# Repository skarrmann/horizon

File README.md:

# Horizon Keyboard

Horizon is a 52 key (4x14) ortholinear keyboard, powered by an Arduino Pro Micro.

This keyboard is a grid of 1U keys with no special features: no hotswap, no RGB, no OLED screen, no knobs.

## Project structure

* [`gerbers`](gerbers): Gerber files for PCB manufacturing
* [`graphics`](graphics): Source assets for PCB silkscreen
* [`kicad`](kicad): KiCad project files (schematics and PCB designs)
* [`kicad-libraries`](kicad-libraries): KiCad components and footprints
* [`kicad-plugins`](kicad-plugins): KiCad Pcbnew Python plugins
* [`images`](images): Images for project documentation

## PCBs

Two separate PCB designs are available for MX and Choc keyswitches, with their respective footprints and key spacing (MX: 19mm x 19mm, Choc: 18mm x 17mm).

Each design consists of a main PCB, a top plate to protect the microcontroller, and a bottom plate to protect the bottom components:

The bottom plate is a cutout of all the components exposed through the bottom of the main PCB, and screws *directly* against the main PCB. This nicely guards you and your desk surface from all the pointy through-hole bits, while retaining a low keyboard height:

## KiCad project notes

The bottom and top plates are generated via a custom KiCad 7 Python SWIG plugin [Horizon Board Producer](kicad-plugins/horizon-board-producer-plugin.py).

For the plugin to generate these plate boards, the PCB and its footprints use the following layer convention:

* `F.Adhesive` designates top plate holes and edge cuts.
* `B.Adhesive` designates bottom plate holes and edge cuts.

When the board producer runs, these layers are used as follows:

* On the board and footprints:
    * Graphics on the plate's designated layer will be moved to `Edge.Cuts` when producing that plate.
    * As with all edge cuts, please make sure your graphics are non-overlapping closed shapes.
* On footprints only:
    * Pads of type "SMD Aperture" and shape "Circular/Oval" on the plate's designated layer will be converted to proper NPTH pads.
    * Note only circular/oval shapes are supported for these pads, because they are the only available hole/drill shapes. If you need a fancy plate cutout shape on your footprint, then draw graphics lines on the designated layer.
    * **IMPORTANT**: When adding pads solely for plate cutout purposes, set the technical layer to just the designated plate cutout layers. Leave all other technical layers unchecked.

Additionally, the board producer plugin will preserve any in-bounds "H" footprint pads (mounting holes), "LOGO" footprint graphics (custom silkscreen art), and board silkscreen on the plates. Other items which are not needed for plates (e.g., copper tracks and zones) are removed from the plates.

The board producer plugin also generates all the Gerber files for production.

Please note the board producer plugin expects the following folder structure:

* The KiCad PCB file is two folders deep from the project root, e.g., `kicad/[board-version]/[board-name].kicad_pcb`
* When the plugin executes, a folder called `temp` is created in the project root to store any temporary files created.
    * Each time the board producer runs, any existing files in this temporary folder are deleted.

**IMPORTANT:** If you would like to use this plugin and plate edge cuts convention for you own project, please make sure you carefully examine the output Gerber files! The plugin ultimately worked well for my case, but you might need to make adjustments to the plugin to suit your project. And to reduce the chance of being charged extra money by PCB manufacturers, use footprint plate holes instead of edge cuts whenever reasonable to do so.

**IMPORTANT:** This plugin uses `pcbnew.LoadBoard()` to load copies of the PCB, which is [not safely supported in a running instance of KiCad](https://forum.kicad.info/t/the-loadboard-function-is-invalid/31238/9). To avoid project integrity problems this may cause to the running KiCad instance, the plugin forcefully exits KiCad upon execution completion.

## Keyboard firmware

* [QMK](https://github.com/qmk/qmk_firmware/tree/master/keyboards/horizon)
* ZMK
    * Horizon shield definition is in [skarrmann's zmk-config](https://github.com/skarrmann/zmk-config)

## Bill of materials

For PCBs, keyswitches, and keycaps, get parts depending on your desired keyswitch type.

Part | Purpose | Quantity | Notes
---- | ------- | -------- | ---------
Main PCB  | circuit board | 1 | Send Gerber zip files to [JLCPCB](https://jlcpcb.com/).
Top plate PCB  | protects microcontroller | 1 |
Bottom plate PCB  | protects bottom pins and components | 1 |
Arduino Pro Micro | Microcontroller board | 1 | Or use another Pro Micro compatible dev board with same dimensions (confirmed Elite-C V4, nice!nano 2.0, SuperMini nRF52840, and Adafruit KB2040 fit)
6x6mm DIP 4-pin tactile switch | Reset button | 1 |
1N4148 SOD-123 | Diodes for keyboard row-column matrix | 52 |
Keyswitches |  | 52 | PCB mount (5 pin) switches recommended. For MX, any switches should work. For Choc, get Choc V1 switches.
Keycaps |  | 52 | For MX, any keycaps should work. For Choc, get those which fit Choc V1 18mm x 17mm
M2 6mm screws | Secure main PCB and plate PCBs | 8 |
M2 nuts | Secure main PCB and plate PCBs | 8 |
M2 8mm male-female standoffs | Raise top plate PCB above microcontroller | 4 |
2mm tall rubber bumpons | Raise board above desk surface and provide skid resitance | 6 |

I recommend using sockets for the Pro Micro. For socketing options, refer to [40% Keyboards' sockets article](https://www.40percent.club/2018/03/sockets.html).

M2 standoff height requirements are dependent on the seated microcontroller height. An M2 spacer set should give you enough options. I recommend getting a reset button ~2mm taller than the M2 standoffs so the button is level with the top plate.

If using a bluetooth Pro Micro compatible dev board, then power it with battery size 301230. On the dev board, use sockets which provide at least 3mm clearance for the battery to fit underneath. Cut the battery wires so they are just long enough to poke through the B-/B+ pins from the underside of the dev board. Solder the battery's black wire to the B- pin, and the red wire to the B+ pin. Use a piece of Kapton or electrical tape to secure the battery to the dev board. When done, the dev board should look something like this:

Horizon does not use a power switch or battery connector, so no other parts are needed when using a bluetooth Pro Micro compatible board. Since there is no physical power switch, refer to [ZMK's power management configuration](https://zmk.dev/docs/config/power) to manage power through firmware features.

## PCB manufacturing settings

These are the manufacturing settings I used when ordering from JLCPCB:

* **Base Material**: FR4
* **Layers**: 2
* **Dimensions**: (whatever the gerber file specifies)
* **PCB Qty**: 5
* **Different Design**: 1
* **Delivery Format**: Single PCB
* **PCB Thickness**: 1.6
* **PCB Color**: Black
* **Silkscreen**: White
* **Surface Finish**: LeadFree HASL-RoHS
* **Outer Copper Weight**: 1 oz
* **Gold Fingers**: No
* **Confirm Production File**: No
* **Flying Probe Test**: Fully Test
* **Castellated Holes**: No
* **Remove Order Number**: Specify a location

**IMPORTANT:** All PCBs have ["JLCJLCJLCJLC" silkscreen text](https://support.jlcpcb.com/article/28-how-to-remove-order-number-from-your-pcb) underneath the Pro Micro footprint. If you want to remove the order number from the boards or you want to print the PCBs with another manufacturer, then I recommend removing this silkscreen text from the `.kicad_pcb` file, and then re-run the Horizon Board Producer plugin to create the updated Gerber files.

## Build tips

* The microcontroller needs to be soldered with the components facing down.
* The main PCB uses a ground plane, so ground pads are more stubborn to solder. Make sure your soldering tip has good surface area coverage across the pad and component leg. If your soldering iron supports it, turning up the temperature a bit can help too.
* Before soldering the keyswitches, make sure they are perfectly straight and fully inserted into the PCB. Put the keycaps on the inserted keyswitches, and give a thorough visual inspection for any spacing or height irregularities between the keycaps. For MX builds, Gateron switches in particular have thicker PCB-mount pins - push these keyswitches in hard to make sure they are fully inserted!
* To get a perfect fit between the main PCB and bottom plate, keep your soldering tidy! Clean any excess solder/flux which falls outside the bounds of the bottom plate cutouts.
* Attaching the main PCB and the bottom plate requires a very steady hand. The approach that worked best for me was using narrow tweezers to grip the edges of the hex nut against the main PCB, while driving in the screw from the bottom plate.
* The top plate is a very tight fit. If the inner keycaps rub against it, first ensure the top plate is perfectly centered. To center it, slide a thin piece of cardstock in-and-out between the inner keycaps and the top plate on all sides. If that does not resolve the keycaps rubbing, then remove the top plate, sand its edges a bit, and try again.

## Revision history

* **Rev1** (2021-07-30 - not publicly released):
    * PCB: Experimental prototype of MX board.
    * Schematic: Wire as 42 key 7x6 matrix (original release only had 6 keys on bottom row).
* **Rev2** (2021-09-26)
    * PCB: Create MX and Choc boards with bottom and top plates.
    * Schematic: Wire as 52 key 4x14 matrix.
* **Rev2.1** (2021-10-24)
    * PCB: Slightly improve thermal relief clearance to make soldering ground pads easier.
* **Rev2.2** (2021-10-25)
    * Horizon Board Producer plugin: Now supports converting designated placeholder pads to NPTH pads during plate generation.
    * Footprints: Replace graphics which indicate plate cutouts with placeholder pads which indicate plate NPTH pads.
    * PCB: Gerber files regenerated using updated board producer plugin.
* **Rev2.3** (2022-03-21)
    * Horizon Board Producer plugin: Upgrade to KiCad 6
    * PCB, Schematic: No physical changes. Files upgraded to KiCad 6, and Gerber files regenerated using updated files.
* **Rev2.4** (2023-11-09)
    * Horizon Board Producer plugin: Upgrade to KiCad 7
    * PCB, Schematic: No physical changes. Files upgraded to KiCad 7, and Gerber files regenerated using updated files.

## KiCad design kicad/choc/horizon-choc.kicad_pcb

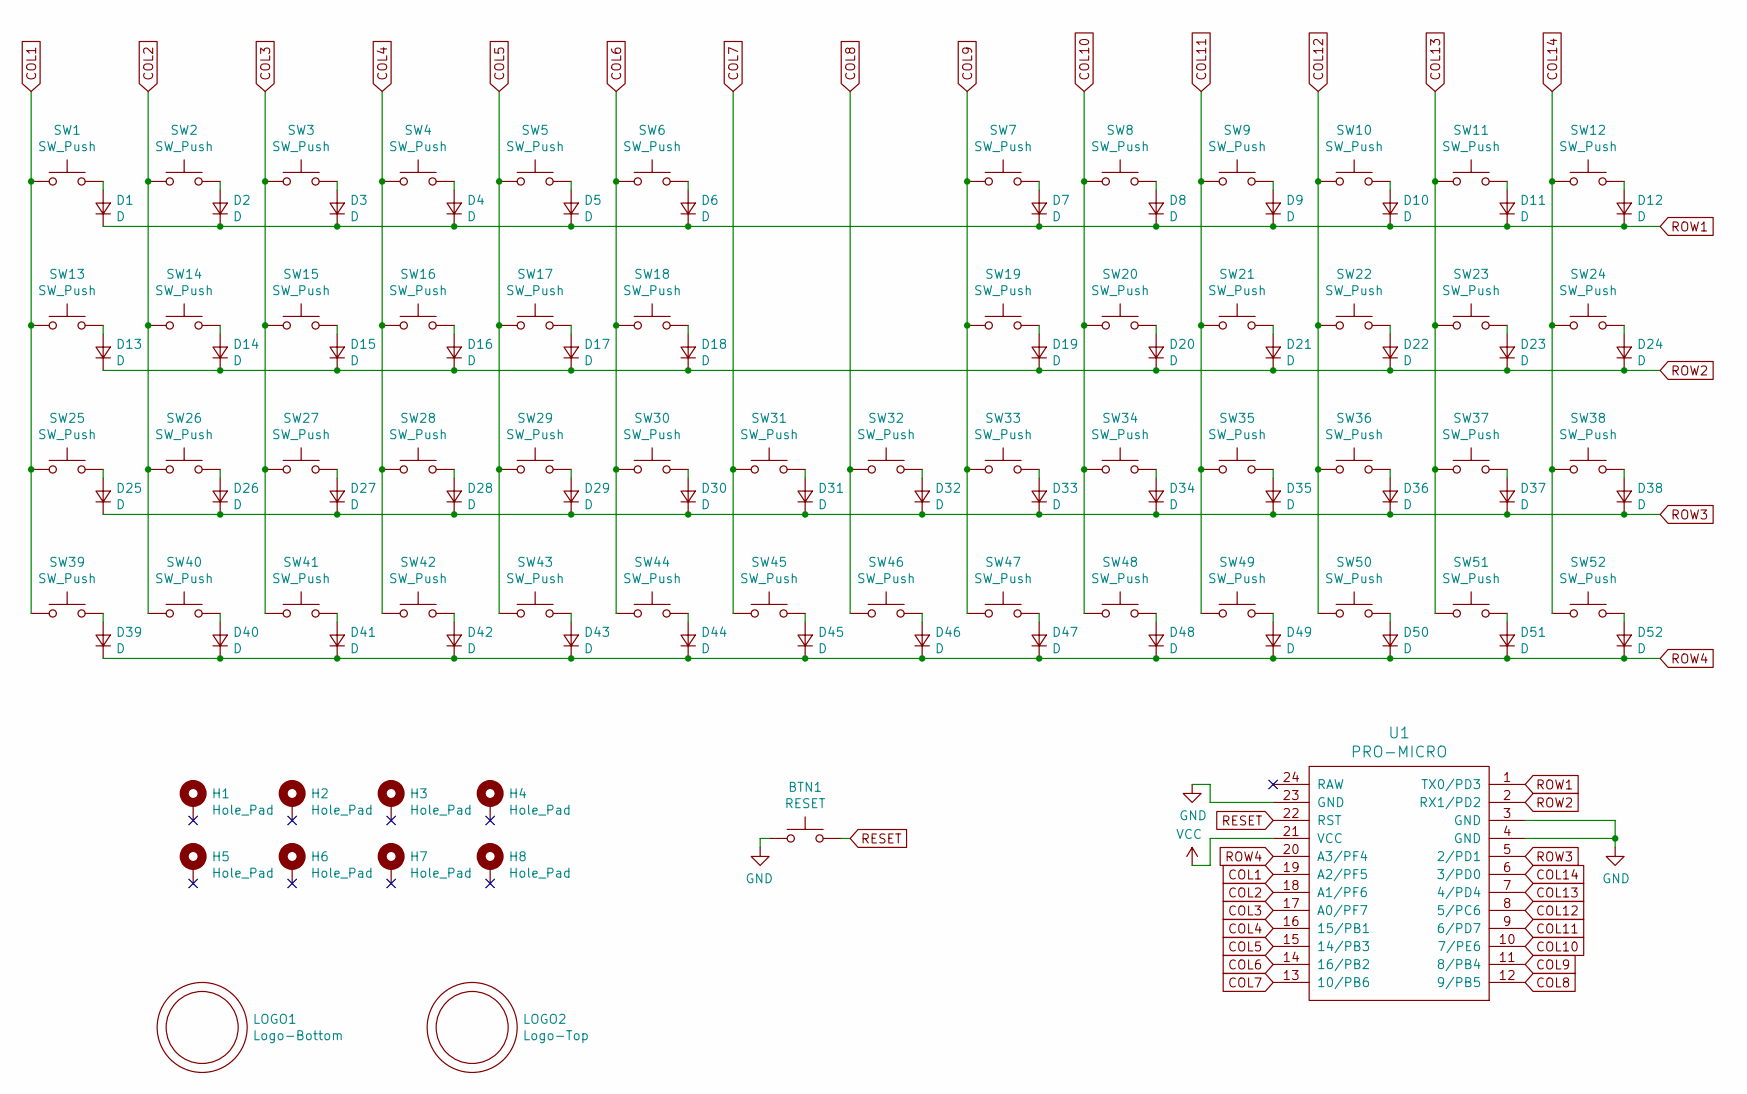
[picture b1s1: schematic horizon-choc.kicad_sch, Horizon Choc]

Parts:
BTN1: RESET; SW_Push_6mm
D1, D2, D3, D4, D5, D6, D7, D8, D9, D10, D11, D12, D13, D14, D15, D16, D17, D18, D19, D20, D21, D22, D23, D24, D25, D26, D27, D28, D29, D30, D31, D32, D33, D34, D35, D36, D37, D38, D39, D40, D41, D42, D43, D44, D45, D46, D47, D48, D49, D50, D51, D52: D; D_SOD-123
H1, H2, H3, H4, H5, H6, H7, H8: Hole_Pad; Mount_M2
LOGO1: Logo-Bottom; Logo_Horizon_Small
LOGO2: Logo-Top; Logo_Horizon_H
SW1, SW2, SW3, SW4, SW5, SW6, SW7, SW8, SW9, SW10, SW11, SW12, SW13, SW14, SW15, SW16, SW17, SW18, SW19, SW20, SW21, SW22, SW23, SW24, SW25, SW26, SW27, SW28, SW29, SW30, SW31, SW32, SW33, SW34, SW35, SW36, SW37, SW38, SW39, SW40, SW41, SW42, SW43, SW44, SW45, SW46, SW47, SW48, SW49, SW50, SW51, SW52: SW_Push; SW_Choc
U1: PRO-MICRO; Pro-Micro

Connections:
COL1: SW1.1, SW13.1, SW25.1, SW39.1, U1.19 (A2/PF5)
COL2: SW2.1, SW14.1, SW26.1, SW40.1, U1.18 (A1/PF6)
COL3: SW3.1, SW15.1, SW27.1, SW41.1, U1.17 (A0/PF7)
COL4: SW4.1, SW16.1, SW28.1, SW42.1, U1.16 (15/PB1)
COL5: SW5.1, SW17.1, SW29.1, SW43.1, U1.15 (14/PB3)
COL6: SW6.1, SW18.1, SW30.1, SW44.1, U1.14 (16/PB2)
COL7: SW31.1, SW45.1, U1.13 (10/PB6)
COL8: SW32.1, SW46.1, U1.12 (9/PB5)
COL9: SW7.1, SW19.1, SW33.1, SW47.1, U1.11 (8/PB4)
COL10: SW8.1, SW20.1, SW34.1, SW48.1, U1.10 (7/PE6)
COL11: SW9.1, SW21.1, SW35.1, SW49.1, U1.9 (6/PD7)
COL12: SW10.1, SW22.1, SW36.1, SW50.1, U1.8 (5/PC6)
COL13: SW11.1, SW23.1, SW37.1, SW51.1, U1.7 (4/PD4)
COL14: SW12.1, SW24.1, SW38.1, SW52.1, U1.6 (3/PD0)
GND: BTN1.2, U1.3 (GND), U1.4 (GND), U1.23 (GND)
unnamed: D1.2 (A), SW1.2
unnamed: D2.2 (A), SW2.2
unnamed: D3.2 (A), SW3.2
unnamed: D4.2 (A), SW4.2
unnamed: D5.2 (A), SW5.2
unnamed: D6.2 (A), SW6.2
unnamed: D7.2 (A), SW7.2
unnamed: D8.2 (A), SW8.2
unnamed: D9.2 (A), SW9.2
unnamed: D10.2 (A), SW10.2
unnamed: D11.2 (A), SW11.2
unnamed: D12.2 (A), SW12.2
unnamed: D13.2 (A), SW13.2
unnamed: D14.2 (A), SW14.2
unnamed: D15.2 (A), SW15.2
unnamed: D16.2 (A), SW16.2
unnamed: D17.2 (A), SW17.2
unnamed: D18.2 (A), SW18.2
unnamed: D19.2 (A), SW19.2
unnamed: D20.2 (A), SW20.2
unnamed: D21.2 (A), SW21.2
unnamed: D22.2 (A), SW22.2
unnamed: D23.2 (A), SW23.2
unnamed: D24.2 (A), SW24.2
unnamed: D25.2 (A), SW25.2
unnamed: D26.2 (A), SW26.2
unnamed: D27.2 (A), SW27.2
unnamed: D28.2 (A), SW28.2
unnamed: D29.2 (A), SW29.2
unnamed: D30.2 (A), SW30.2
unnamed: D31.2 (A), SW31.2
unnamed: D32.2 (A), SW32.2
unnamed: D33.2 (A), SW33.2
unnamed: D34.2 (A), SW34.2
unnamed: D35.2 (A), SW35.2
unnamed: D36.2 (A), SW36.2
unnamed: D37.2 (A), SW37.2
unnamed: D38.2 (A), SW38.2
unnamed: D39.2 (A), SW39.2
unnamed: D40.2 (A), SW40.2
unnamed: D41.2 (A), SW41.2
unnamed: D42.2 (A), SW42.2
unnamed: D43.2 (A), SW43.2
unnamed: D44.2 (A), SW44.2
unnamed: D45.2 (A), SW45.2
unnamed: D46.2 (A), SW46.2
unnamed: D47.2 (A), SW47.2
unnamed: D48.2 (A), SW48.2
unnamed: D49.2 (A), SW49.2
unnamed: D50.2 (A), SW50.2
unnamed: D51.2 (A), SW51.2
unnamed: D52.2 (A), SW52.2
RESET: BTN1.1, U1.22 (RST)
ROW1: D1.1 (K), D2.1 (K), D3.1 (K), D4.1 (K), D5.1 (K), D6.1 (K), D7.1 (K), D8.1 (K), D9.1 (K), D10.1 (K), D11.1 (K), D12.1 (K), U1.1 (TX0/PD3)
ROW2: D13.1 (K), D14.1 (K), D15.1 (K), D16.1 (K), D17.1 (K), D18.1 (K), D19.1 (K), D20.1 (K), D21.1 (K), D22.1 (K), D23.1 (K), D24.1 (K), U1.2 (RX1/PD2)
ROW3: D25.1 (K), D26.1 (K), D27.1 (K), D28.1 (K), D29.1 (K), D30.1 (K), D31.1 (K), D32.1 (K), D33.1 (K), D34.1 (K), D35.1 (K), D36.1 (K), D37.1 (K), D38.1 (K), U1.5 (2/PD1)
ROW4: D39.1 (K), D40.1 (K), D41.1 (K), D42.1 (K), D43.1 (K), D44.1 (K), D45.1 (K), D46.1 (K), D47.1 (K), D48.1 (K), D49.1 (K), D50.1 (K), D51.1 (K), D52.1 (K), U1.20 (A3/PF4)

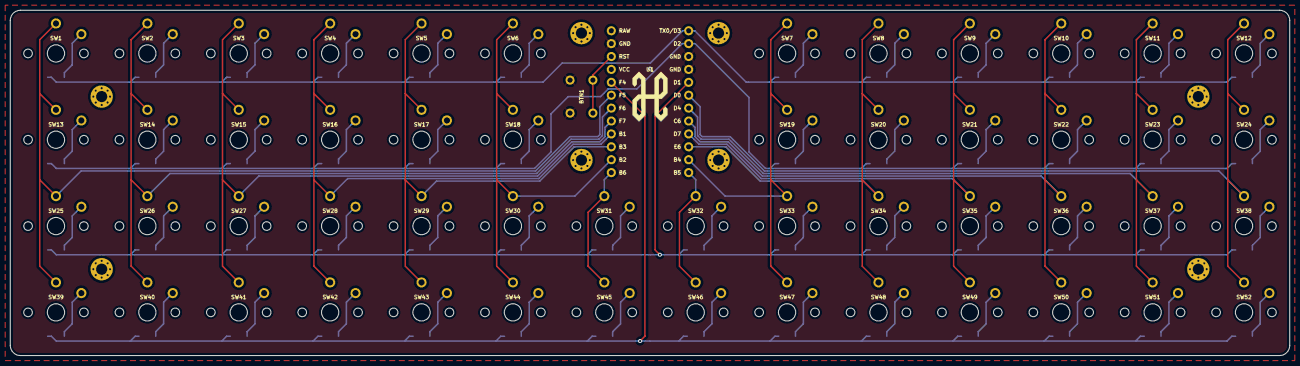
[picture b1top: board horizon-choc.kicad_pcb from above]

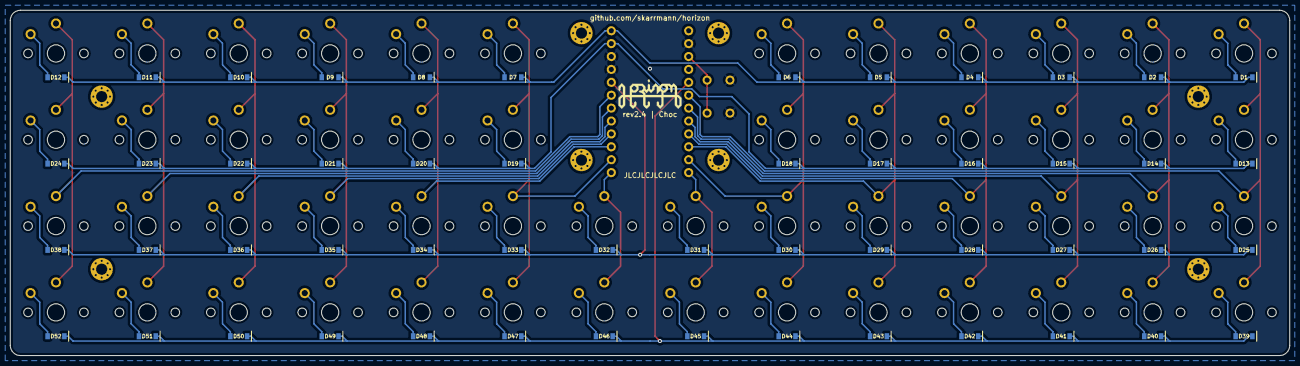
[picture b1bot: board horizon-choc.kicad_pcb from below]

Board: 2 copper layers, 252.0 x 68.0 mm, 116 parts (53 on the bottom side), 72 nets.

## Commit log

2021-08-09 Fix relative path of gerber file output
2021-08-22 Begin revision 2
2021-08-24 Create bottom plate board. Begin laying out Choc switch board. Clean up footprints and remove unused ones
2021-08-25 Adjust center component layout for MX and Choc consistency.
2021-08-26 Route traces on choc version
2021-08-28 Route Choc board with diodes in center
2021-09-03 Use 50 key layout on MX version
2021-09-04 Clean up MX version before overhaul
2021-09-06 Implement battery on Choc version, plus bottom and top PCBs
2021-09-08 Use 50-key layout
2021-09-12 Layout MX PCB
2021-09-13 Mark bottom plate cutout on footprint adhesive layer. Begin writing bottom plate generation script
2021-09-13 Distinguish between top and bottom cuts with front/back adhesive layers
2021-09-13 Mark top and bottom plate border edge cuts on boards with adhesive layers
2021-09-18 Update plate outlines. Remove battery from Choc design for now
2021-09-19 Clean up plate cuts, update MX board with battery removed
2021-09-20 Create board producer script to generate plates, gerbers, and drill files
2021-09-20 Write usage instructions for board producer script
2021-09-21 Convert board generator script into KiCAD PcbNew plugin
2021-09-25 Preserve logos on plate PCBs
2021-09-25 Remove unused footprints and other files. Update readme. Prepare for production!
2021-09-25 Remove generated files
2021-09-25 Only output gerber zip files in gerbers folder, and put all other production files in gitignored temp folder
2021-09-26 Note extra PCB charge from JLCPCB
2021-10-09 Add photos and clean up readme
2021-10-09 Fix KiCAD plugin URL in readme
2021-10-09 Additional readme cleanup
2021-10-10 Note QMK keyboard definition is an open PR
2021-10-11 Add build note about keyswitch insertion (Gateron MX in particular)
2021-10-11 Update firmware listing with QMK repo link
2021-10-11 Add rubber bumpons to BOM
2021-10-13 Remove unused schematic symbols
2021-10-13 Add title block to schematic and PCB files
2021-10-16 Update readme with project structure, PCB manufacturing settings
2021-10-16 Rename photos to images
2021-10-16 Fix JLCPCB Gerber preview note
2021-10-16 Change PCB design file page size to A4
2021-10-21 Use relative paths for KiCad libraries. Fix name case on push button footprint
2021-10-23 Document board producer code and add MIT copyright header
2021-10-24 Add notes about using LiPo battery, and clarify pro micro board support)
2021-10-24 PCB revision 2.1, document revisions
2021-10-24 Format revision history
2021-10-26 Rev 2.2 - Update board producer to support footprint NPTH creation for plates
2021-10-26 Non-functional change: Clean up internal order of MX switch footprint pads
2021-10-26 Update board producer to use oval holes drill mode - use alternate drill mode for JLCPCB (https://support.jlcpcb.com/article/149-how-to-generate-gerber-and-drill-files-in-kicad)
2021-10-27 Clean up board producer temp path to ensure stale files are not included in Gerber zip
2021-10-28 Update ZMK firmware status
2021-11-15 Ensure board producer temp folder exists before cleaning
2021-12-09 Document plugin's expected folder structure.
2021-12-26 Check for existence of plate bounds before generating plate
2022-01-03 Clarify current KiCad version support
2022-02-05 Experiment with KiCad 6 migration (plugin currently fails)
2022-03-19 Resave Choc board with updated library footprints
2022-03-19 Get producer plugin 'working' to the point of not segfaulting. It still produces bad output
2022-03-20 Create functional plugin which creates new boards (not copies of the main) for the plates
2022-03-21 Get the plugin working with the modify existing board copy approach. Currently-opened project is still mutated as unwanted side effect
2022-03-21 Handle board copy with file system. Show complete dialog when plugin finishes
2022-03-21 Gitignore KiCad backups folder
2022-03-21 Update projects to KiCad 6 and regenerate gerbers
2022-03-21 Upgrade revision to 2.3. Remove KiCad 5 files
2022-03-21 Update KiCad project notes to reflect KiCad 6 changes
2022-03-21 Clarify 2.3 makes no physical changes to PCB and schematic
2022-03-21 Use KiCad 6 symbol library format
2022-03-22 Remove obsolete note about manufacturing cost
2022-06-25 Update keyswitch and keycaps vendor URLs
2022-07-22 Update BOM vendor links
2023-11-02 Change switch vendor.
2023-11-02 Remove vendor URLs
2023-11-10 Upgrade plugin and project files to KiCad 7
2024-02-27 Add build tip for the microcontroller orientation
2024-09-28 Add bluetooth dev board battery installation notes and photo
2024-09-28 Note there is no power switch or battery connector, link to ZMK power management configuraton
